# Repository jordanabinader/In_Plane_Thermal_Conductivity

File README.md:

# In-Plane Thermal Conductivity Project

## Table of Contents
- [In-Plane Thermal Conductivity Project](#in-plane-thermal-conductivity-project)
  - [Table of Contents](#table-of-contents)
  - [Description](#description)
  - [Project Structure](#project-structure)
  - [Using the Repository](#using-the-repository)
    - [Installation](#installation)
    - [Running the program](#running-the-program)
    - [Exiting the program](#exiting-the-program)
  - [Database Schema](#database-schema)
  - [TC08 Note](#tc08-note)

## Description
This project integrates various components such as server, database, web application, controls, and computations for in-plane thermal conductivity analysis. It utilizes a robust Node.js server and a responsive front-end built with Next.js alongside several python scripts communicating with the hardware.

## Project Structure
- **Client**: Implements the user interface using Next.js and manages HTTP requests with axios.
- **Server**: A Node.js server employing Express.js for HTTP requests and connecting to an SQLite3 database, with database manipulation facilitated by Knex.
- **Control**: A collection of python scripts dedicated to recording the data from the thermocouples, controlling the heaters, and calculating the thermal conductivity
  - *Thermal Control*
    - Pico_Talker.py: Setting the duty cycle of the heaters based on the control mode set by the user in the website.
  - *Thermocouple*
    - writeFromDAQ.py: Recieves the data from the TC-08 DAQ and writes the temperatures to the temperature table in the database
    - graphLive.py: Plots the live temperature data along side calculated sin fit for active tests.
    - graphFull.py: Similar functionality to graphLive.py but for looking at the data of previous tests. 

## Using the Repository

### Installation

1. Update and upgrade ubuntu packages
  ```
  sudo apt update && sudo apt upgrade
  ```
2. Install picosdk and drivers for the Pico Logger TC-08. Instructions from: https://www.picotech.com/downloads/linux
  ```
  sudo bash -c 'wget -O- https://labs.picotech.com/Release.gpg.key | gpg --dearmor > /usr/share/keyrings/picotech-archive-keyring.gpg'
  sudo bash -c 'echo "deb [signed-by=/usr/share/keyrings/picotech-archive-keyring.gpg] https://labs.picotech.com/picoscope7/debian/ picoscope main" >/etc/apt/sources.list.d/picoscope7.list'
  sudo apt-get update
  sudo apt-get install libusbtc08
  ```

3. Install Python 3.11
  ```
  sudo apt install python3.11
  ```
4. Install pip
  ```
  sudo apt install python3-pip
  ```

5. Install venv pip package
  ```
  python3.11 -m pip install venv
  ```
6. Install curl
  ```
  sudo apt install curl
  ```
7. Install nvm  
  ```
  curl -o- https://raw.githubusercontent.com/nvm-sh/nvm/v0.39.6/install.sh | bash
  source ~/.bashrc
  ```
8. Install Node LTS 20.10.0 and specify it as default
  ```
  nvm install 20.10.0
  nvm alias default 20.10.0
  ```

9. **Clone the repository**: <!-- Replace git clone command with one specifying version once its released -->
  ```
  git clone https://github.com/jordanabinader/In_Plane_Thermal_Conductivity.git
  cd In_Plane_Thermal_Conductivity/
  ```
10. **Setup the python virtual environment**
  ```
  python3.11 -m venv iptc_venv
  ```
  
11. **Install node dependencies**:
   - For the client:
       ```
       cd client
       npm install
       cd ../
       ```
   - For the server:
       ```
       cd server
       npm install
       cd ../
       ```
12. **Install python dependencies**
  ```
  source iptc_venv/bin/activate
  python3.11 -m pip install -r requirements.txt
  ```

### Running the program
Your current working directory should be the base folder of the In_Plane_Thermal_Conductivity repository

1. Activate the virtual environment
  ```
  source iptc_venv/bin/activate
  ```
2. Check the serial port
  ```
  ls -l /dev/serial/by-id
  ```
  The raspberry pi pico likely defaults to ttyACM0, but if not change the ttyACM0 in the command below to what this command highlights

3. Start everything up
  ```
  python3.11 Startup.py --serial-port /dev/ttyACM0
  ```

### Exiting the program
1. In the terminal window running Startup.py from the command above, hit `ctrl+c`
  
   - A normal exit will look similar to below

   - If you see more than 3 or 4 print statments in a row that say `{SOMETHING} not shutting down`  the heater control board should be unplugged from and the computer restarted as this means that something went wrong in the shutdown process and the heaters can cause damage if left running while powered

It is also worthwhile to check the terminal output after ending a test to ensure that the heaters get turned off the the thermocouple DAQ gets deactivated properly. The terminal output at the end of a test should look something like the image below. Similar to the what happens when the whole system gets shutdown: If you see more than 3 or 4 print statments in a row that say `{SOMETHING} not shutting down`  the heater control board should be unplugged from and the computer restarted as this means that something went wrong in the shutdown process and the heaters can cause damage if left running while powered. 

## Database Schema
The application uses the following SQLite3 database schemas:

- **Test Settings Table** (`testSettingTableName`):
  - `controlMode`: Float
  - `frequency`: Float
  - `amplitude`: Float
  - `datetime`: DateTime

- **Power Table** (`powerTableName`):
  - `heaterNum`: Float
  - `mV`: Float
  - `mA`: Float
  - `dutyCycle`: Float
  - `datetime`: DateTime

- **Temperature Table** (`temperatureTableName`):
  - `datetime`: DateTime (Default to current time)
  - `relTime`: Float
  - `temp1` to `temp8`: Float (temperature readings for 8 different points)

## TC08 Note
For use with TC-08, you may have to modify library.py of picosdk so it can manually find the installed library

ex. "/Library/Frameworks/Python.framework/Versions/3.12/lib/python3.12/site-packages/picosdk/library.py"

Edit the first line after def _load(self):

library_path = find_library(self.name) ->
library_path = '/Library/Frameworks/PicoSDK.framework/Libraries/libusbtc08/libusbtc08.dylib' For running on Charlie's Macbook Pro

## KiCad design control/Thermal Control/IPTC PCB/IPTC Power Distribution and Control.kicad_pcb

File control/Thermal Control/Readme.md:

# Thermal Control
This folder contains the code necessary to control the heaters connected to the In-Plane Thermal Conductivity (IPTC) Power Distribution and Control PCB that integrates with the larger Web App

## Getting Started
Instructions for how to get started using the power distribution and control PCB and heater control software
### Pico_Talker
Pico_Talker.py is the python script that controls the power output of the heaters.

#### Instructions

1. Install Python. This code was tested to run on Python 3.11.6 and Python 3.11.5
1. Install required packages with: `pip install -r requirements.txt`
1. Run the script with `python Pico_Talker.py {ARGUMENTS}` with the desired arguments. See the arguments section below. 

#### Arguments

For instructions on how to use optional arguments [see this documentation from python](https://docs.python.org/3/howto/argparse.html#introducing-optional-arguments).

Example: `python Pico_Talker.py --port COM4 --baud 115200 --database storage.db`

**--port:** Optional
- Serial Port the IPTC Power Distribution and Control PCB is connected to
- If no port is passed, it uses the Serial_Helper.terminalChooseSerialDevice() to get user input on which port to use

**--baud:** Optional. Default = 115200
- Baud rate that the IPTC Power Distribution and Control PCB is communicating at.
- Shouldn't be changed unless you have made changes to the arduino code

**--database:** Optional. Default "your_database.db"
- The relative path to the database relative to the current working directory of this python script (where the script was started from), or the absolute path on the computer

### IPTC Power Distribution and Control PCB and Arduino Code
This PCB was designed after initial assemblies on protoboards had hazards in the form of insufficient ampacity of the wires use. This PCB also greatly simplified the assembly and reduced the risk of shorts. To make your own, the suggested manufacturer is JLCPCB as that is what the design rules are for and where this project ordered from. To order the exact same thing, upload the [IPTC Power Distribution and Control Fabrication Output zip file](IPTC%20PCB/IPTC%20Power%20Distribution%20and%20Control%20Fabrication%20Output.zip) to JLCPCB. Our order specifications were as follows:
- 2 Layer Board
- 1.6mm thickness
- 1 oz outer copper weight
- HASL (with lead) 

The code, in the [IPTC_heater_control](IPTC_heater_control/) folder, can be uploaded directly to the Raspberry Pi Pico on the PCB. Although the PCB has pins broken out for SPI, intended for MAX31855KASA breakout boards, the arduino code and Pico_Talker.py in the current state does not support the use of these pins. If you wish to add this functionality, make the changes necessary and submit a pull-request to the repository. In order to make the addition as seamless as possible, follow the [Serial Communication Pattern](Serial%20Communication%20Pattern.md).

In order to upload the code to the PCB, you need to use the Arduino Mbed OS RP2040 Boards from the Boards Manager in the Arduino IDE and [install the Adafruit INA-260 library](https://learn.adafruit.com/adafruit-ina260-current-voltage-power-sensor-breakout/arduino#install-adafruit-ina260-library-3024064)

## Web Interface

Although this script has a couple endpoints, it isn't a webpage that is human readable, the endpoints are just for the primary website to send put requests to to tell Pico_Talker.py to update internal states, such as the current test settings and if the test has ended. Do not send HTTP requests to these endpoints unless you know what your are doing because it could have unintended side effects.

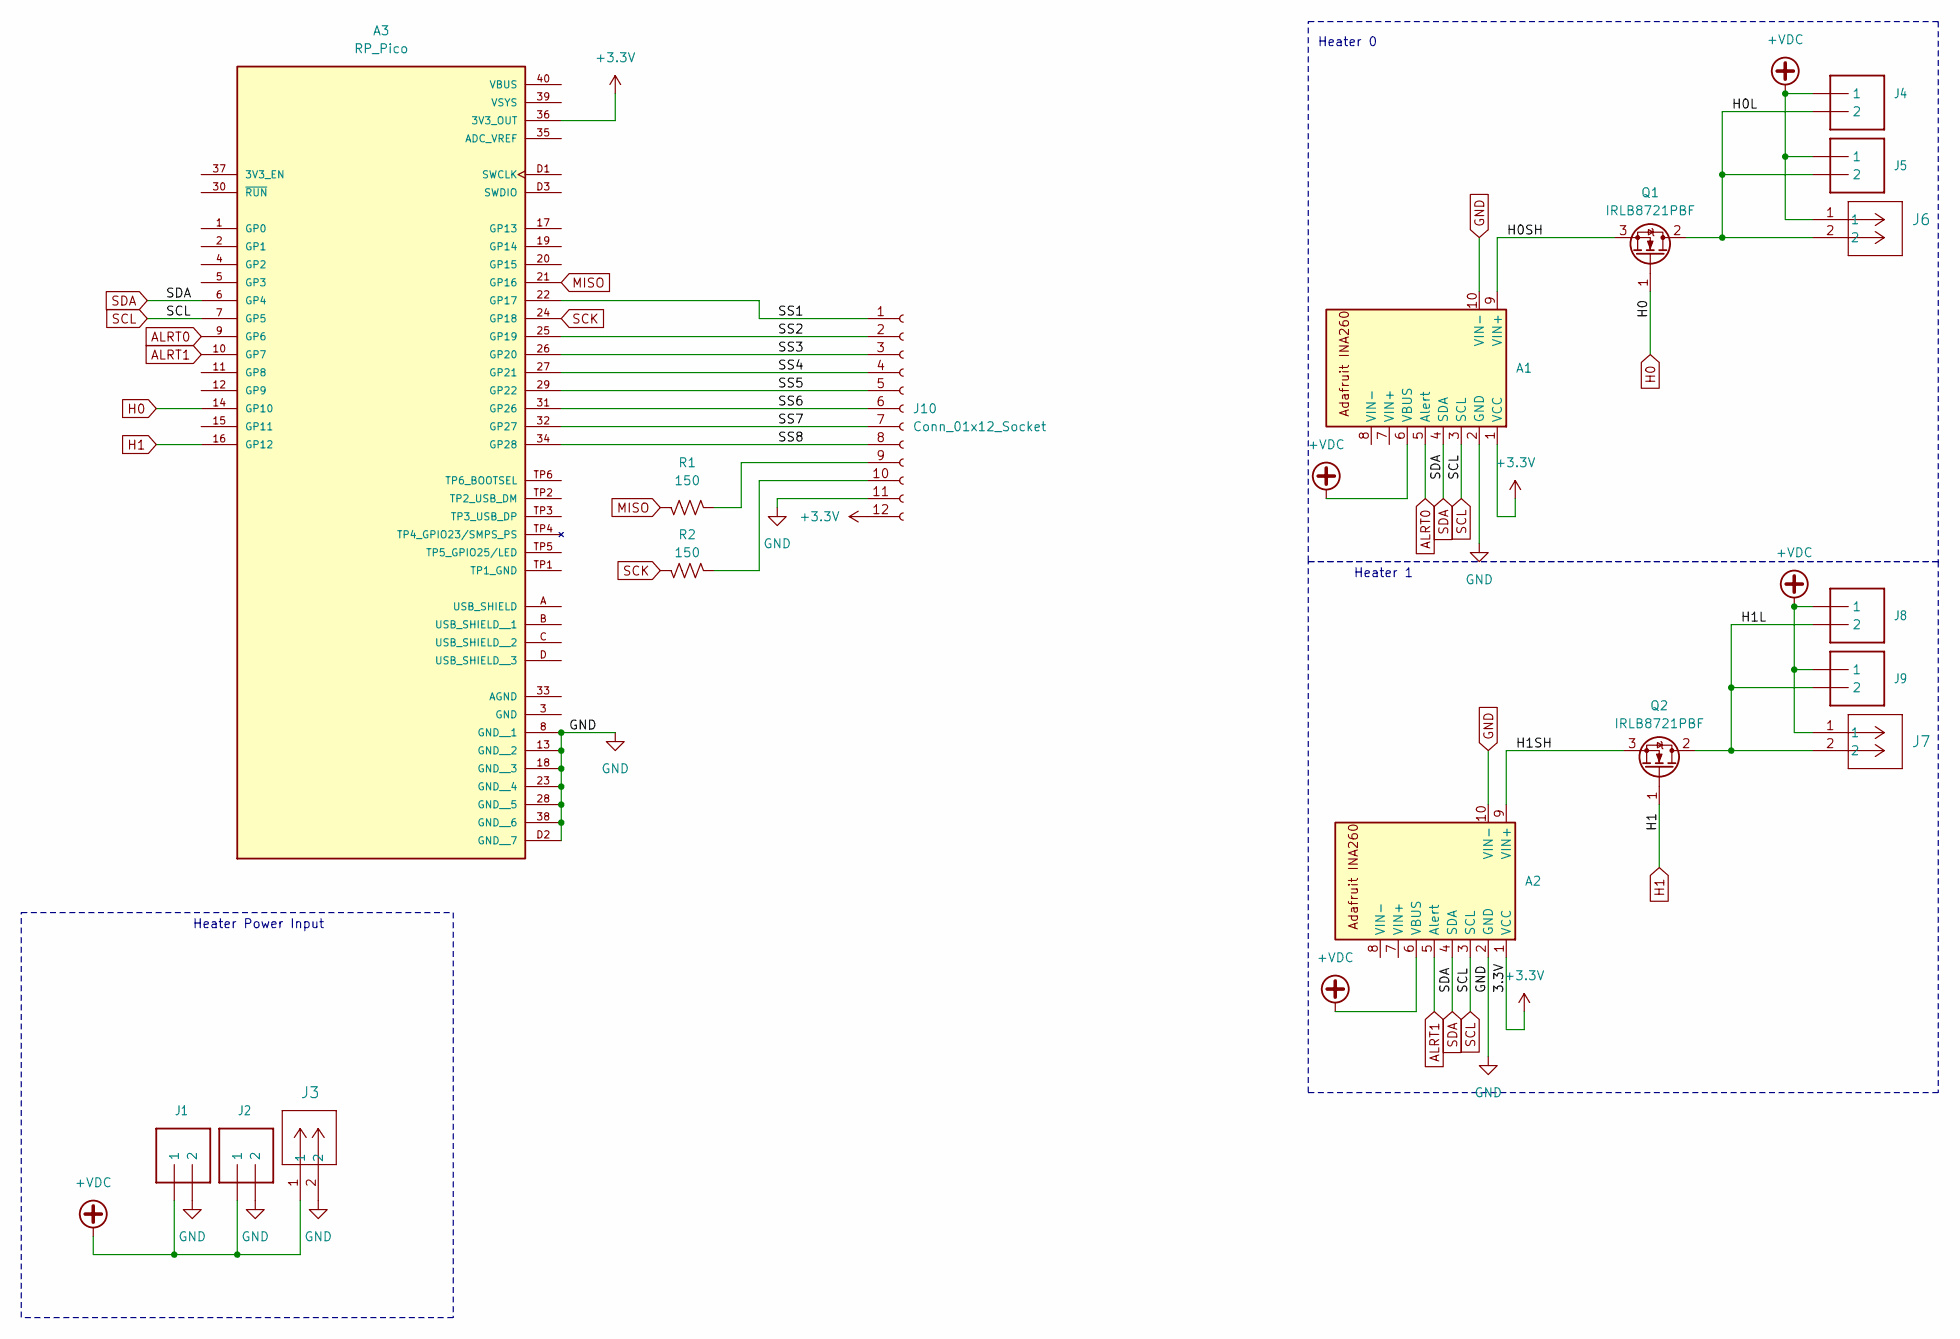
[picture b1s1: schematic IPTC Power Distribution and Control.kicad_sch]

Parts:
A1, A2: Adafruit_INA260
A3: RP_Pico; PARTREV 1.9
J1, J4, J8: SMD_PAD_1X2_4MMx3MM; SMDPAD_1x2_4MMx3MM
J2, J5, J9: TERMBLOCK_508_1X2
J3, J6, J7: OSTVN02A150; CONN_OSTVN02A150_OST
J10: Conn_01x12_Socket; PinHeader_1x12_P2.54mm_Vertical
Q1, Q2: IRLB8721PBF; TO-220-3_Vertical
R1, R2: 150; R_0603_1608Metric_Pad0.98x0.95mm_HandSolder

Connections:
+3.3V: A1.1 (VCC), A2.1 (VCC), A3.36 (3V3_OUT), J10.12
+VDC: A1.6 (VBUS), A2.6 (VBUS), J1.2 (1), J2.P$3 (1), J3.1, J4.2 (1), J5.P$3 (1), J6.1, J7.1, J8.2 (1), J9.P$3 (1)
/H0L: J4.1 (2), J5.P$4 (2), J6.2, Q1.2 (D)
/H0SH: A1.9 (VIN+), Q1.3 (S)
/H1L: J7.2, J8.1 (2), J9.P$4 (2), Q2.2 (D)
/H1SH: A2.9 (VIN+), Q2.3 (S)
/SS1: A3.22 (GP17), J10.1
/SS2: A3.25 (GP19), J10.2
/SS3: A3.26 (GP20), J10.3
/SS4: A3.27 (GP21), J10.4
/SS5: A3.29 (GP22), J10.5
/SS6: A3.31 (GP26), J10.6
/SS7: A3.32 (GP27), J10.7
/SS8: A3.34 (GP28), J10.8
ALRT0: A1.5 (Alert), A3.9 (GP6)
ALRT1: A2.5 (Alert), A3.10 (GP7)
GND: A1.2 (GND), A1.10 (VIN-), A2.2 (GND), A2.10 (VIN-), A3.8 (GND__1), A3.13 (GND__2), A3.18 (GND__3), A3.23 (GND__4), A3.28 (GND__5), A3.38 (GND__6), A3.D2 (GND__7), J1.1 (2), J2.P$4 (2), J3.2, J10.11
H0: A3.14 (GP10), Q1.1 (G)
H1: A3.16 (GP12), Q2.1 (G)
MISO: A3.21 (GP16), R1.2
unnamed: J10.9, R1.1
unnamed: J10.10, R2.1
SCK: A3.24 (GP18), R2.2
SCL: A1.3 (SCL), A2.3 (SCL), A3.7 (GP5)
SDA: A1.4 (SDA), A2.4 (SDA), A3.6 (GP4)

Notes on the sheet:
Heater 1
Heater Power Input
Heater 0

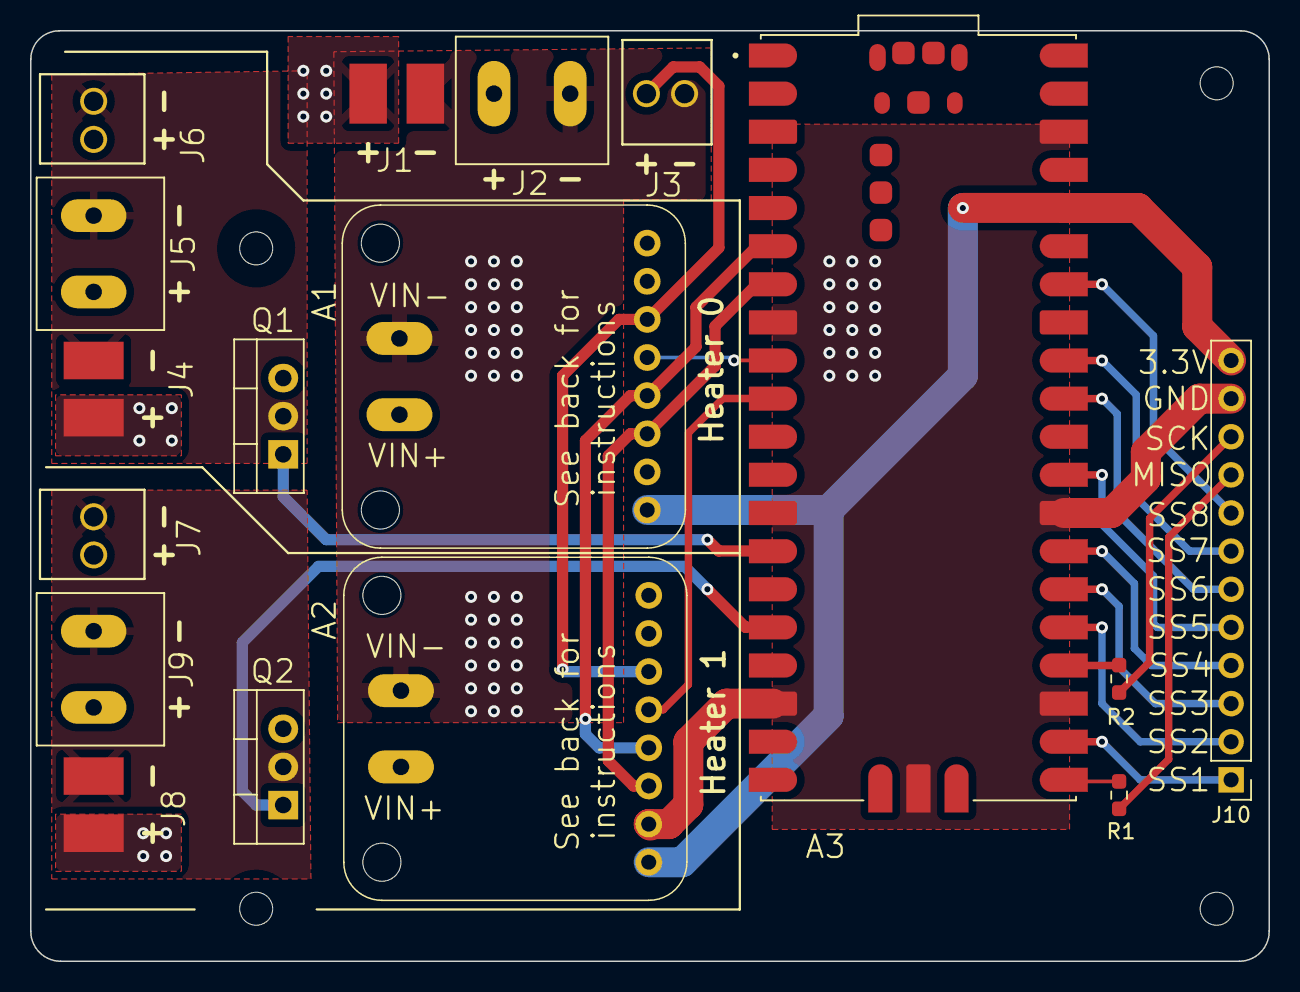
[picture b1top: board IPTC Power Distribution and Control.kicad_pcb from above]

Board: 2 copper layers, 82.5 x 62.0 mm, 17 parts (0 on the bottom side), 25 nets.

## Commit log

2023-11-30 Initial commit with client and server
2023-11-30 Readme
2023-11-30 init
2023-11-30 test-setting-function
2023-11-30 test-setting-integration
2023-12-01 fixed_testGraph
2023-12-01 removed DS
2023-12-01 Fixed Readme
2023-12-01 Add Thermal Control Files
    Thermal Control files copied over from legacy repo "Capstone_NEU_inPLane_ThermalCond" to centralize all the files to run the script.
2023-12-01 Create Startup.py
    Startup.py is a python script designed to start up the webserver and wait for the webserver to tell it to boot up the Pico_Talker and any other required scripts when a test is beginning.
2023-12-01 Add Pico_Talker alive endpoint
2023-12-01 Add script status checking functionality to test start
2023-12-01 Add startTestHandler doc string
2023-12-01 Update readme for thermal controls and startup script
2023-12-01 move python requirements file
2023-12-01 filter
2023-12-02 adding TC graphing
2023-12-02 moving TC folder, minor changes
2023-12-02 edited sqlite queries
2023-12-02 minor fix
2023-12-02 more minor fixes
2023-12-02 test_setup
2023-12-02 query fixes
2023-12-02 bug fixes
2023-12-02 bug fix in testGraph, update writefromCSV
2023-12-02 bug fix
2023-12-02 bug fixes and catches
2023-12-02 removing data processing for now
2023-12-02 catching 0 errors
2023-12-02 removing bug testing modes
2023-12-02 removing print statements
2023-12-02 add frq change functionality to graphFull
2023-12-02 adding endpoint to graphLive
2023-12-02 fix processing on graphFull
2023-12-02 control_modes to lower case to match db schema
2023-12-02 TC graphing, daq reading, and test-end endpoint
2023-12-02 Signal handler to close everything on SIGTERM
2023-12-02 style edits
2023-12-02 Fix Hz to rad/s conversion
2023-12-02 moving legend on graphFull
2023-12-02 complete graphFull functionality
2023-12-03 Try adding CORS support to Pico_Talker
2023-12-04 added functionality, extensive bug fixes
2023-12-04 add aiohttp CORS to startup py
2023-12-04 add CORS support to graphLive for alive check
2023-12-04 Change to port 2999 and added loader and functionalities
2023-12-04 Fiexd table filtering
2023-12-04 Added update to active column on db
2023-12-04 Implemented check if test inputs are good
2023-12-04 Wrong inputs
2023-12-04 Error box for inputs
2023-12-04 Change Popen commands to lists
2023-12-04 Fix list formatting for start commands
2023-12-04 reorder creating event loops
2023-12-04 change python command to 3.11 to avoid aliases
2023-12-04 box error fix
2023-12-04 get_event_loop to new_event_loop
2023-12-04 Implemnented delete functionality
2023-12-04 Debugging Updates
2023-12-04 Switch test-start endpoint to Startup.py
2023-12-04 remove alive endpoint checks and wait 5s
2023-12-04 Add terminate print output
2023-12-04 send test-end to Startup.py
2023-12-05 Duty Cycle and controlMode fix
2023-12-05 Switch manual control from duty cycle to power output
    Previously manual control interpreted the amplitude column of the database as a duty cycle to send to both heaters, however that could be confusing so this switches manual control to interpreting the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
2023-12-05 Added manual option with db connection
2023-12-05 add better handling for closing out processes
2023-12-05 tiggle fix
2023-12-05 minor production fix
2023-12-05 FIxed the loading and test graph bg
2023-12-05 change default database path to actual relative path
2023-12-05 Update Readme.md for proper installation and startup
2023-12-05 fix hz to radian typo with **
2023-12-05 graph buffer update fix
2023-12-05 doubling periods to view
2023-12-05 added sort and serach pagination feature
2023-12-05 Autodetect frequency to use and show selected time
    Added BoxAnnotation to top graph to make seeing what time span is selected to display in the bottom graph
2023-12-05 Live Data now uses more datapoints
    Also added BoxAnnotation to show what time segment is displayed on the fitted data
2023-12-05 Change bokeh version to fix BoxAnnotation error
    https://github.com/bokeh/bokeh/issues/13432
2023-12-05 Use actual value to define BoxAnnotation not source
2023-12-05 Revert graphLive Changes to displaying more data
2023-12-06 halfway through updating times and temps
2023-12-06 finish renaming variables, add box annotation
2023-12-06 Live plot now shows larger range
    Fitted plot displays the last 5 periods or 5000 datapoints, whichever is larger
2023-12-06 Fix BoxAnnotation
2023-12-06 Added gracefulExit to close the graphing scripts
    Flask and or bokeh changes the default python handling of SIGINT and or SIGTERM so sometimes the ctrl+c command doesn't end the script.
    This commit corrects that for graphLive and graphFull
2023-12-06 flip order cut/fit data
2023-12-06 Add venv creation instructions to README
2023-12-06 fixed scrolling
2023-12-06 fixed db path
2023-12-06 Update TestConstant.js
    Loading possible fix
2023-12-06 Don't fit temperature sine with small num points
2023-12-06 Shader stops at current time
    fitted_range_shader now ends at the current time instead of extending to the edge of the graph
2023-12-06 Added live test and can't start already test
2023-12-06 fixed git
2023-12-06 graphLive now uses port 8125
    switch graphLive port to new port so that graphLive and graphFull can run simultaneously
2023-12-06 Chang Startup logic with graphFull and graphLive
    graphFull and graphLive now exist simultaneously so update test start, test end and startup logic to allow for that to be true.
2023-12-07 Update README with new graphing lifecycle
2023-12-07 Added the active test functionality
2023-12-07 clean up node_module files
2023-12-07 modify gitignore to ignore node_modules and pycache
2023-12-07 Fix gitignore node_modules typo
2023-12-13 Update TestGraph Component port
2023-12-21 Update Startup.py
    Add default serial port path
2023-12-21 tiny bug fix
2023-12-21 Update Thermal Control README for new img location
2023-12-21 Add script exiting info to global README
2024-01-10 add vertical lines for test setting change
2024-01-12 db conductivity column typo fix
2024-01-12 Add tracking for last used time span for prev test
2024-01-13 Fixed sorting functionality
2024-01-14 Bugs fix
    Delete, sort, freq and amp functionality
